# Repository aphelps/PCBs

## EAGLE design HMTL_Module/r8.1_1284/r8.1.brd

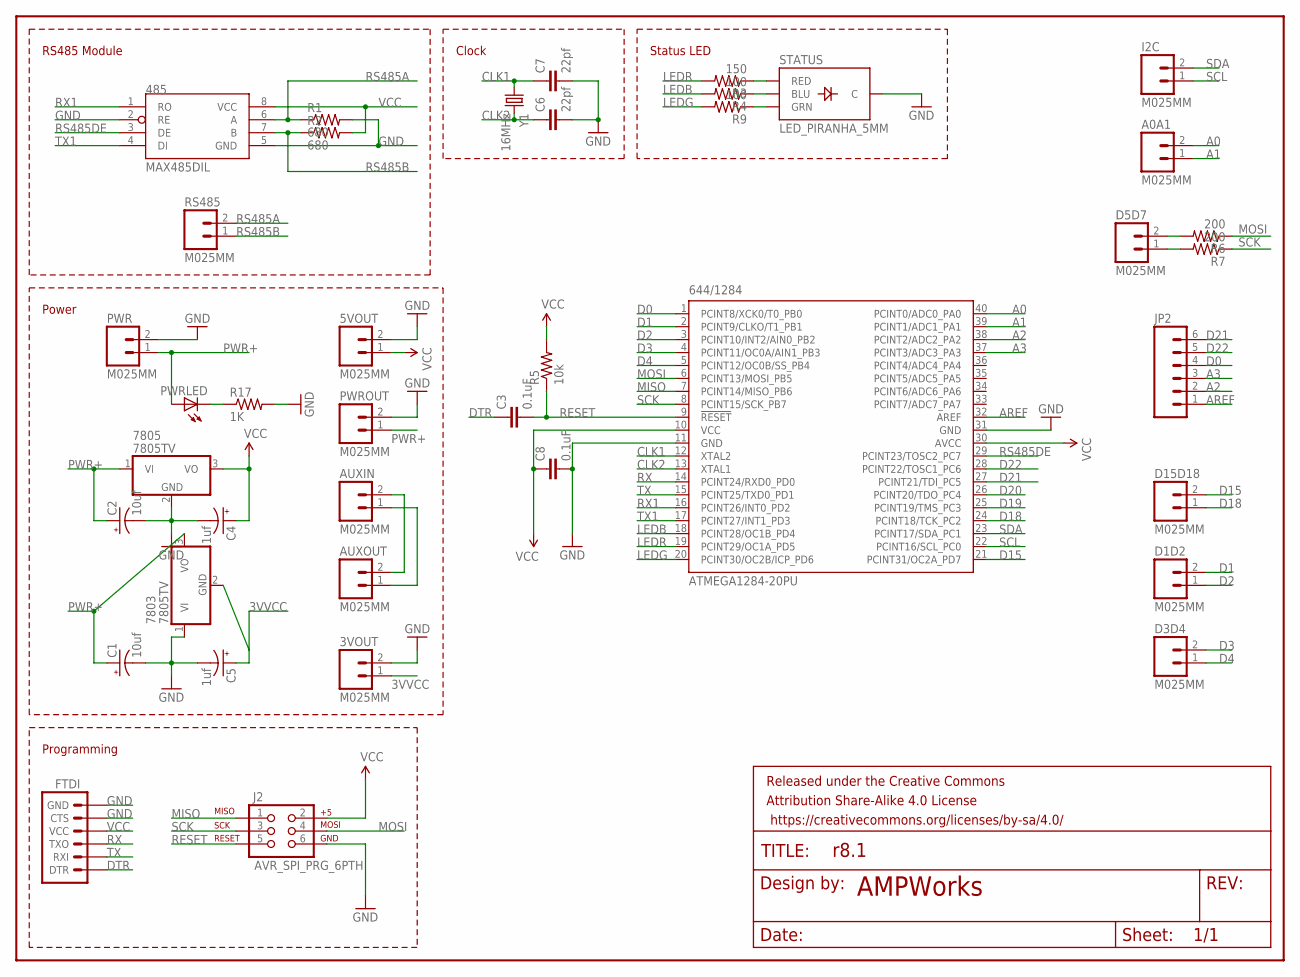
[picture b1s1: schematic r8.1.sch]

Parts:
3VOUT, 5VOUT: M025MM; SCREWTERMINAL-5MM-2
485: MAX485DIL; DIL08
644/1284: ATMEGA1284-20PU; DIL40
7803, 7805: 7805TV; TO220V
A0A1: M025MM; SCREWTERMINAL-5MM-2
AUXIN: M025MM; SCREWTERMINAL-5MM-2
AUXOUT: M025MM; SCREWTERMINAL-5MM-2
C1, C2: 10uf; CPOL-RADIAL-10UF-25V
C3, C8: 0.1uF; CAP-PTH-SMALL
C4, C5: 1uf; CPOL-RADIAL-10UF-25V
C6, C7: 22pf; CAP-PTH-SMALL
D1D2, D3D4, D5D7, D15D18: M025MM; SCREWTERMINAL-5MM-2
FRAME1: FRAME-LETTER; CREATIVE_COMMONS
FTDI: ARDUINO_SERIAL_PROGRAMPTH; 1X06
I2C: M025MM; SCREWTERMINAL-5MM-2
J2: AVR_SPI_PRG_6PTH; 2X3
JP2: M06NO_SILK; 1X06_NO_SILK
PWR: M025MM; SCREWTERMINAL-5MM-2
PWRLED: LED5MM
PWROUT: M025MM; SCREWTERMINAL-5MM-2
R1, R2: 680; AXIAL-0.4
R3: 150; AXIAL-0.4
R4, R9: 100; AXIAL-0.4
R5: 10k; AXIAL-0.4
R6, R7: 200; AXIAL-0.4
R17: 1K; AXIAL-0.4
RS485: M025MM; SCREWTERMINAL-5MM-2
STATUS: LED_PIRANHA_5MM
Y1: 16MHz; HC49US

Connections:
3VVCC: 3VOUT.1, 7803.2 (GND), C5.1 (+)
A0: 644/1284.40 (PCINT0/ADC0_PA0), A0A1.2
A1: 644/1284.39 (PCINT1/ADC1_PA1), A0A1.1
A2: 644/1284.38 (PCINT2/ADC2_PA2), JP2.2
A3: 644/1284.37 (PCINT3/ADC3_PA3), JP2.3
AREF: 644/1284.32 (AREF), JP2.1
CLK1: 644/1284.12 (XTAL2), C7.1, Y1.1
CLK2: 644/1284.13 (XTAL1), C6.1, Y1.2
D0: 644/1284.1 (PCINT8/XCK0/T0_PB0), JP2.4
D1: 644/1284.2 (PCINT9/CLKO/T1_PB1), D1D2.2
D2: 644/1284.3 (PCINT10/INT2/AIN0_PB2), D1D2.1
D3: 644/1284.4 (PCINT11/OC0A/AIN1_PB3), D3D4.2
D4: 644/1284.5 (PCINT12/OC0B/SS_PB4), D3D4.1
D15: 644/1284.21 (PCINT31/OC2A_PD7), D15D18.2
D18: 644/1284.24 (PCINT18/TCK_PC2), D15D18.1
D19: 644/1284.25 (PCINT19/TMS_PC3)
D20: 644/1284.26 (PCINT20/TDO_PC4)
D21: 644/1284.27 (PCINT21/TDI_PC5), JP2.6
D22: 644/1284.28 (PCINT22/TOSC1_PC6), JP2.5
DTR: C3.1, FTDI.DTR
GND: 3VOUT.2, 5VOUT.2, 485.2 (RE), 485.5 (GND), 644/1284.11 (GND), 644/1284.31 (GND), 7803.1 (VI), 7805.2 (GND), C1.2 (-), C2.2 (-), C4.2 (-), C5.2 (-), C6.2, C7.2, C8.2, FTDI.CTS, FTDI.GND, J2.6, PWR.2, PWROUT.2, R1.P$2 (2), R17.P$2 (2), STATUS.- (C)
LEDB: 644/1284.18 (PCINT28/OC1B_PD4), R4.P$2 (2)
LEDG: 644/1284.20 (PCINT30/OC2B/ICP_PD6), R9.P$2 (2)
LEDR: 644/1284.19 (PCINT29/OC1A_PD5), R3.P$2 (2)
MISO: 644/1284.7 (PCINT14/MISO_PB6), J2.1
MOSI: 644/1284.6 (PCINT13/MOSI_PB5), J2.4, R6.P$1 (1)
unnamed: PWRLED.K (C), R17.P$1 (1)
unnamed: AUXIN.1, AUXOUT.1
unnamed: AUXIN.2, AUXOUT.2
unnamed: D5D7.2, R6.P$2 (2)
unnamed: R3.P$1 (1), STATUS.R (RED)
unnamed: R4.P$1 (1), STATUS.B (BLU)
unnamed: R9.P$1 (1), STATUS.G (GRN)
unnamed: D5D7.1, R7.P$2 (2)
PWR+: 7803.3 (VO), 7805.1 (VI), C1.1 (+), C2.1 (+), PWR.1, PWRLED.A, PWROUT.1
RESET: 644/1284.9 (!RESET), C3.2, J2.5, R5.P$1 (1)
RS485A: 485.6 (A), R1.P$1 (1), RS485.2
RS485B: 485.7 (B), R2.P$1 (1), RS485.1
RS485DE: 485.3 (DE), 644/1284.29 (PCINT23/TOSC2_PC7)
RX: 644/1284.14 (PCINT24/RXD0_PD0), FTDI.TXO
RX1: 485.1 (RO), 644/1284.16 (PCINT26/INT0_PD2)
SCK: 644/1284.8 (PCINT15/SCK_PB7), J2.3, R7.P$1 (1)
SCL: 644/1284.22 (PCINT16/SCL_PC0), I2C.1
SDA: 644/1284.23 (PCINT17/SDA_PC1), I2C.2
TX: 644/1284.15 (PCINT25/TXD0_PD1), FTDI.RXI
TX1: 485.4 (DI), 644/1284.17 (PCINT27/INT1_PD3)
VCC: 5VOUT.1, 485.8 (VCC), 644/1284.10 (VCC), 644/1284.30 (AVCC), 7805.3 (VO), C4.1 (+), C8.1, FTDI.VCC, J2.2, R2.P$2 (2), R5.P$2 (2)

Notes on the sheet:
RS485 Module
Programming
Power
AMPWorks
Clock
Status LED

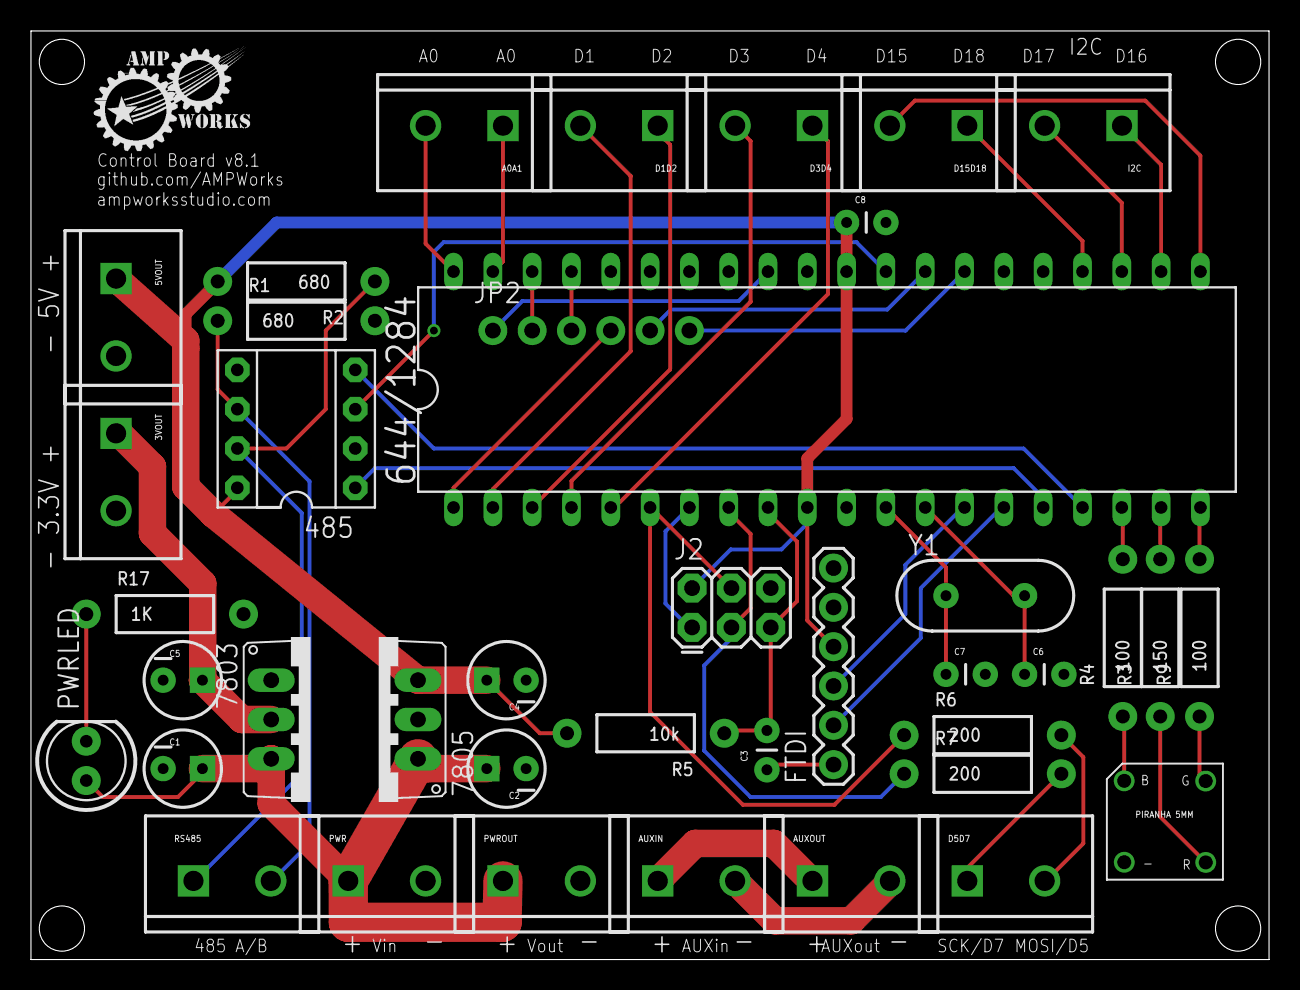
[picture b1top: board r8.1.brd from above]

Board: 2 copper layers, 80.0 x 60.0 mm, 41 parts (0 on the bottom side), 45 nets.

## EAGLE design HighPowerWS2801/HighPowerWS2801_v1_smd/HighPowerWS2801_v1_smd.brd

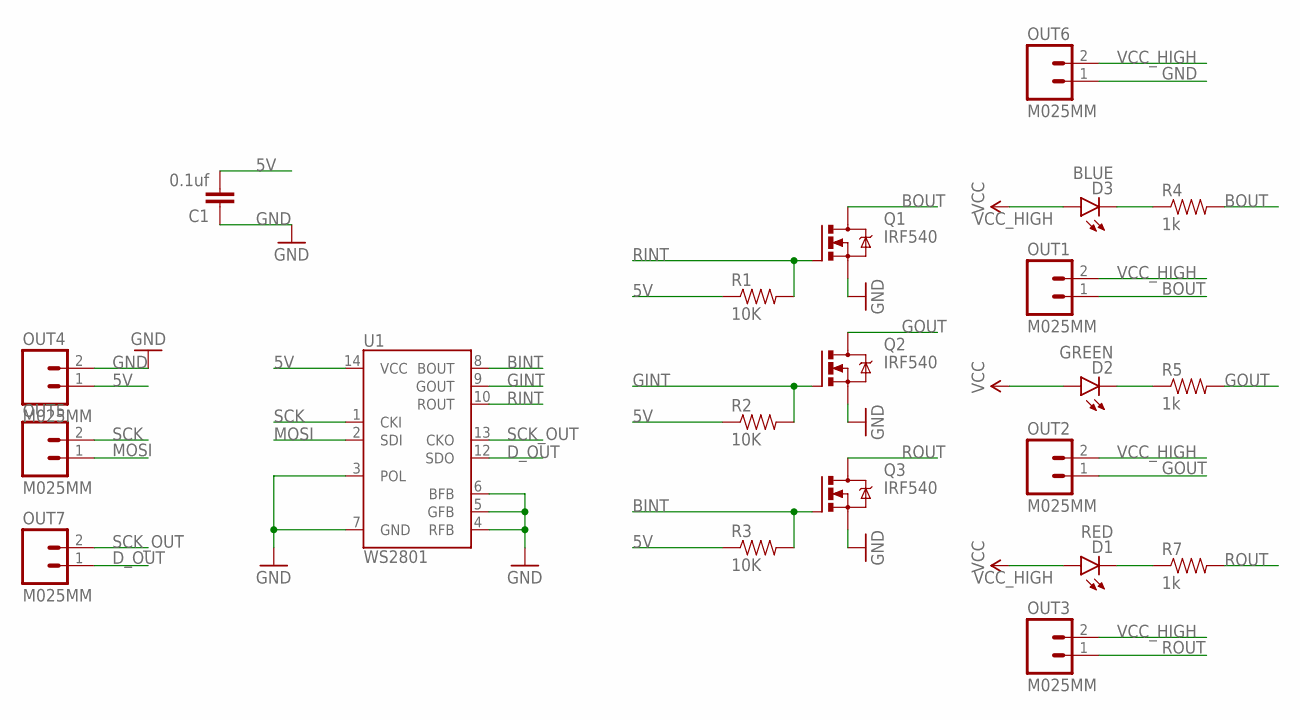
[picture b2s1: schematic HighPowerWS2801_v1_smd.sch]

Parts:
C1: 0.1uf; 0603-CAP
D1: RED; LED-0603
D2: GREEN; LED-0603
D3: BLUE; LED-0603
OUT1, OUT2, OUT3, OUT4, OUT5, OUT6, OUT7: M025MM; SCREWTERMINAL-5MM-2
Q1, Q2, Q3: IRF540; TO220BV
R1, R2, R3: 10K; 0603-RES
R4, R5, R7: 1k; 0603-RES
U1: WS2801; SOP-14

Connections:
5V: C1.2, OUT4.1, R1.1, R2.1, R3.1, U1.14 (VCC)
BINT: Q3.G, R3.2, U1.8 (BOUT)
BOUT: OUT1.1, Q1.D, R4.2
D_OUT: OUT7.1, U1.12 (SDO)
GINT: Q2.G, R2.2, U1.9 (GOUT)
GND: C1.1, OUT4.2, OUT6.1, Q1.S, Q2.S, Q3.S, U1.3 (POL), U1.4 (RFB), U1.5 (GFB), U1.6 (BFB), U1.7 (GND)
GOUT: OUT2.1, Q2.D, R5.2
MOSI: OUT5.1, U1.2 (SDI)
unnamed: D3.C, R4.1
unnamed: D2.C, R5.1
unnamed: D1.C, R7.1
RINT: Q1.G, R1.2, U1.10 (ROUT)
ROUT: OUT3.1, Q3.D, R7.2
SCK: OUT5.2, U1.1 (CKI)
SCK_OUT: OUT7.2, U1.13 (CKO)
VCC_HIGH: D1.A, D2.A, D3.A, OUT1.2, OUT2.2, OUT3.2, OUT6.2

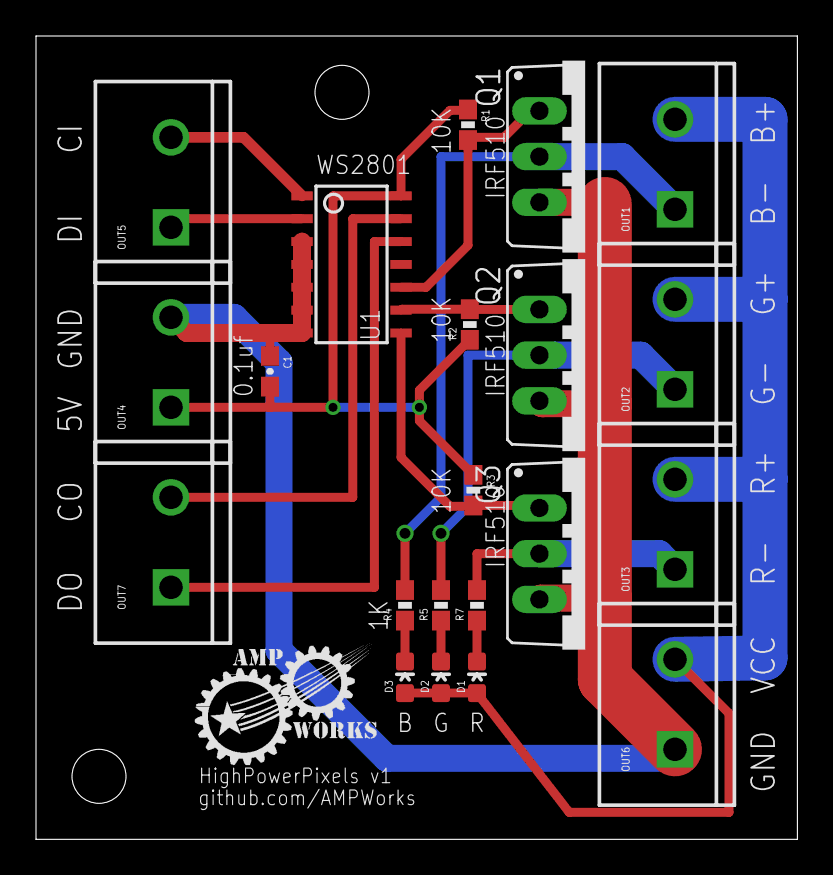
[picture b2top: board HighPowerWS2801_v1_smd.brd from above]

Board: 2 copper layers, 42.3 x 44.6 mm, 21 parts (0 on the bottom side), 16 nets.

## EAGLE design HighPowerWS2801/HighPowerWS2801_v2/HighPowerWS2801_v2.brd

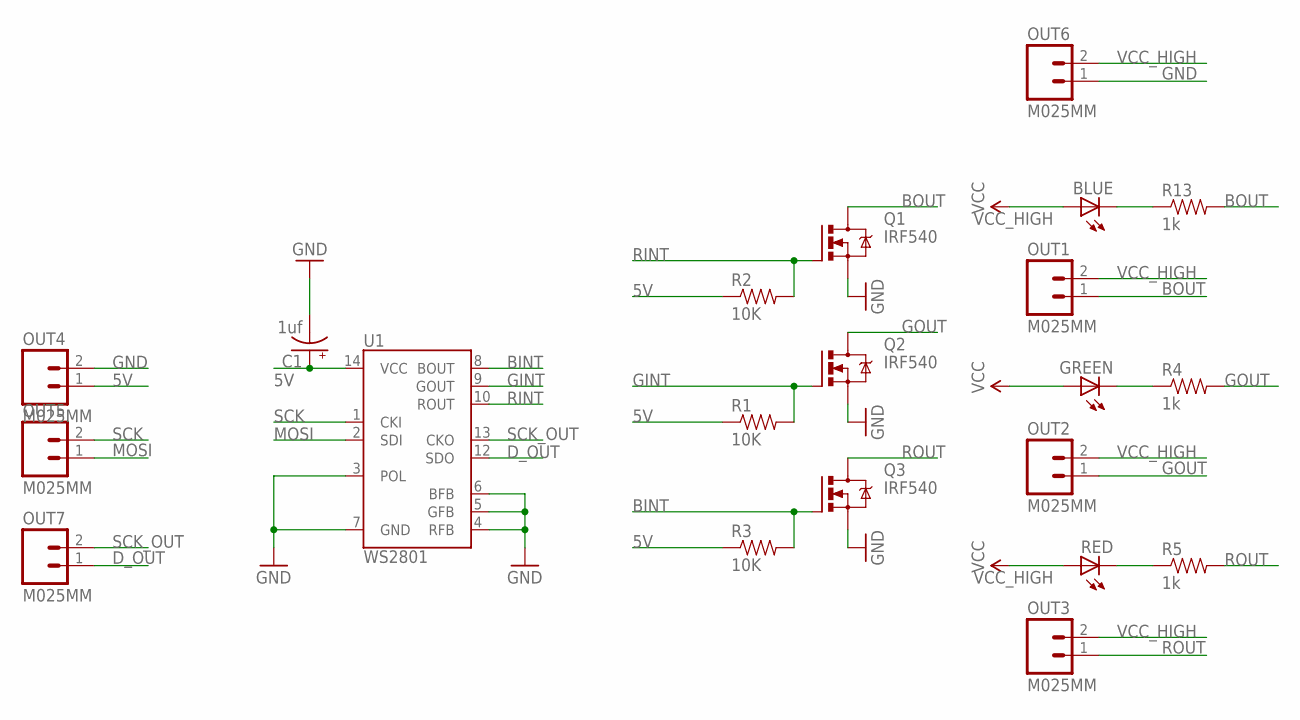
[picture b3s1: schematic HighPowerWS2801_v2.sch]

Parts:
BLUE: LED3MM
C1: 1uf; CPOL-RADIAL-10UF-25V
GREEN: LED3MM
OUT1, OUT2, OUT3, OUT4, OUT5, OUT6, OUT7: M025MM; SCREWTERMINAL-5MM-2
Q1, Q2, Q3: IRF540; TO220BV
R1, R2, R3: 10K; AXIAL-0.4
R4, R5, R13: 1k; AXIAL-0.4
RED: LED3MM
U1: WS2801; SOP-14

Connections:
5V: C1.1 (+), OUT4.1, R1.P$1 (1), R2.P$1 (1), R3.P$1 (1), U1.14 (VCC)
BINT: Q3.G, R3.P$2 (2), U1.8 (BOUT)
BOUT: OUT1.1, Q1.D, R13.P$2 (2)
D_OUT: OUT7.1, U1.12 (SDO)
GINT: Q2.G, R1.P$2 (2), U1.9 (GOUT)
GND: C1.2 (-), OUT4.2, OUT6.1, Q1.S, Q2.S, Q3.S, U1.3 (POL), U1.4 (RFB), U1.5 (GFB), U1.6 (BFB), U1.7 (GND)
GOUT: OUT2.1, Q2.D, R4.P$2 (2)
MOSI: OUT5.1, U1.2 (SDI)
unnamed: BLUE.K (C), R13.P$1 (1)
unnamed: GREEN.K (C), R4.P$1 (1)
unnamed: R5.P$1 (1), RED.K (C)
RINT: Q1.G, R2.P$2 (2), U1.10 (ROUT)
ROUT: OUT3.1, Q3.D, R5.P$2 (2)
SCK: OUT5.2, U1.1 (CKI)
SCK_OUT: OUT7.2, U1.13 (CKO)
VCC_HIGH: BLUE.A, GREEN.A, OUT1.2, OUT2.2, OUT3.2, OUT6.2, RED.A

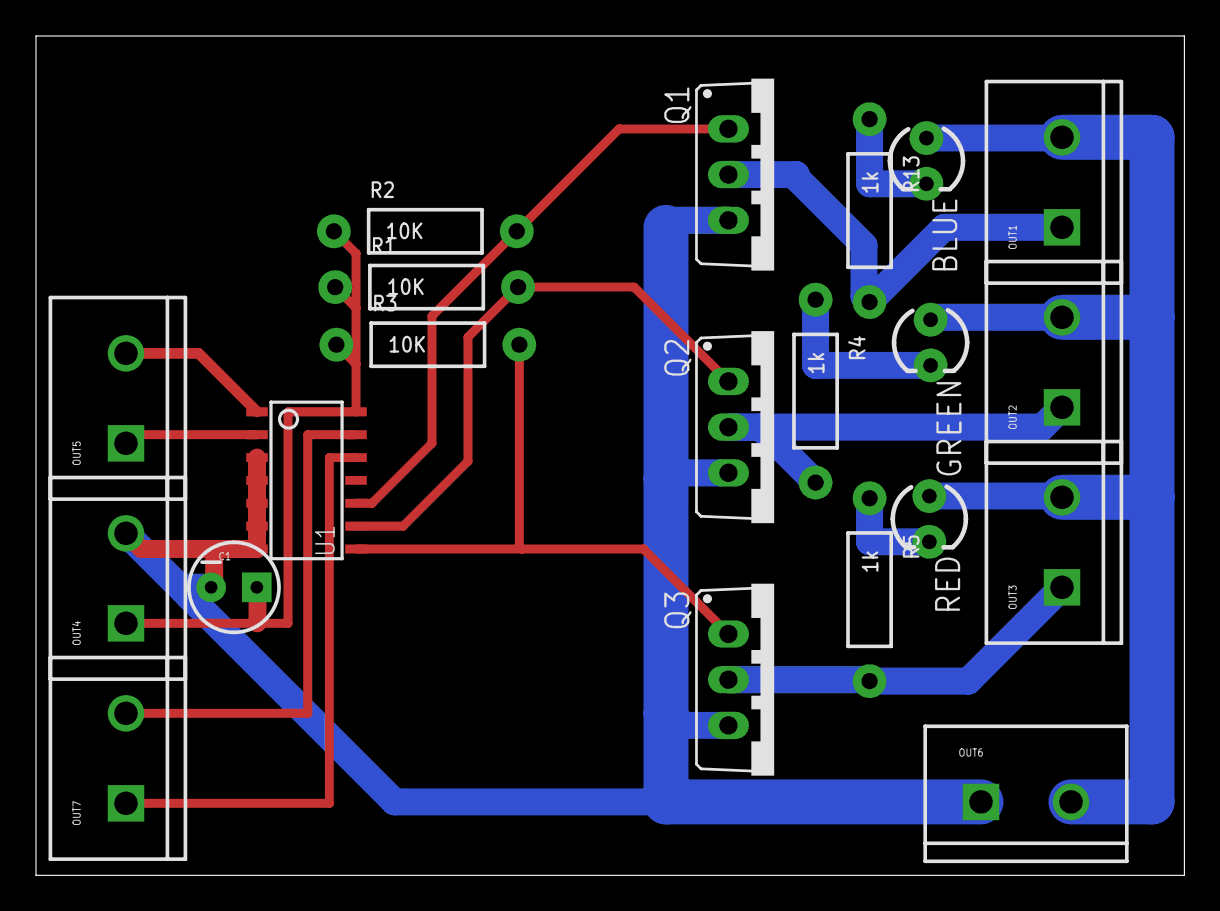
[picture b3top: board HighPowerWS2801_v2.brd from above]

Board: 2 copper layers, 63.8 x 46.6 mm, 21 parts (0 on the bottom side), 16 nets.

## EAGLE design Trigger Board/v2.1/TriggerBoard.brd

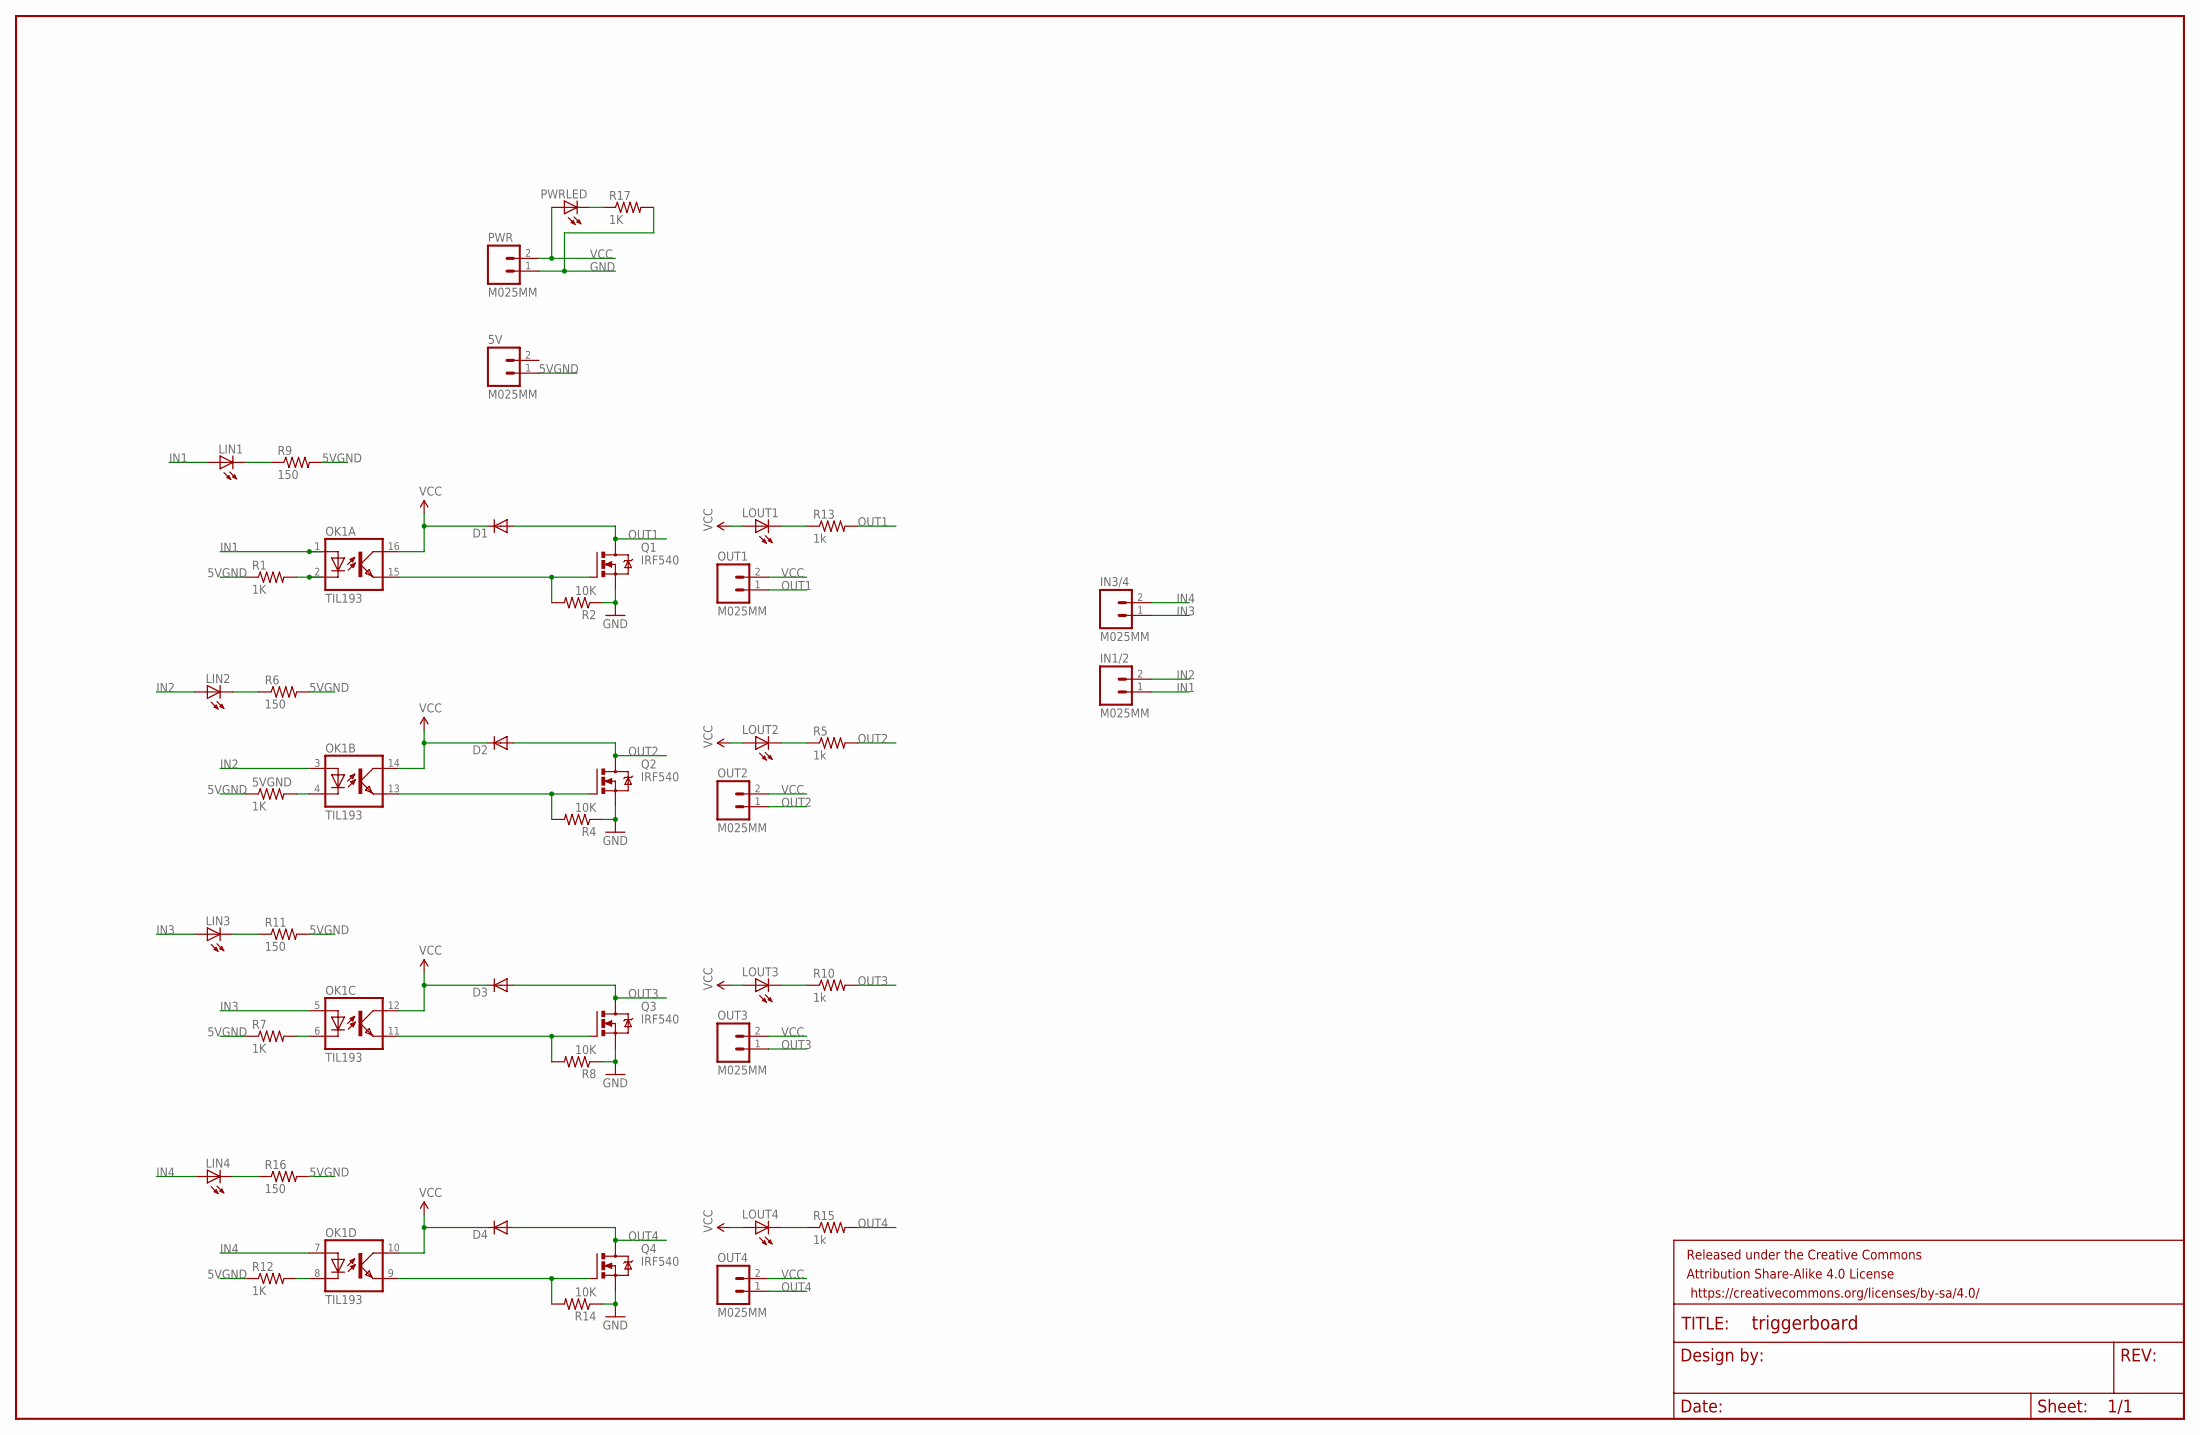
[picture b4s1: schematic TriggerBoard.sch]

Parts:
5V: M025MM; SCREWTERMINAL-5MM-2
5VGND: 1K; AXIAL-0.4
D1, D2, D3, D4: DIODEPTH; DIODE-1N4001
FRAME1: FRAME-LEDGER; CREATIVE_COMMONS
IN1/2, IN3/4: M025MM; SCREWTERMINAL-5MM-2
LIN1, LIN2, LIN3, LIN4: LED3MM
LOUT1, LOUT2, LOUT3, LOUT4: LED3MM
OK1: TIL193; DIL16
OUT1, OUT2, OUT3, OUT4: M025MM; SCREWTERMINAL-5MM-2
PWR: M025MM; SCREWTERMINAL-5MM-2
PWRLED: LED5MM
Q1, Q2, Q3, Q4: IRF540; TO220BV
R1, R7, R12, R17: 1K; AXIAL-0.4
R2, R4, R8, R14: 10K; AXIAL-0.4
R5, R10, R13, R15: 1k; AXIAL-0.4
R6, R9, R11, R16: 150; AXIAL-0.4

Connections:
5VGND: 5V.1, 5VGND.P$1 (1), R1.P$1 (1), R6.P$2 (2), R7.P$1 (1), R9.P$2 (2), R11.P$2 (2), R12.P$1 (1), R16.P$2 (2)
GND: PWR.1, Q1.S, Q2.S, Q3.S, Q4.S, R2.P$1 (1), R4.P$1 (1), R8.P$1 (1), R14.P$1 (1), R17.P$2 (2)
IN1: IN1/2.1, LIN1.A, OK1.1 (A)
IN2: IN1/2.2, LIN2.A, OK1.3 (A)
IN3: IN3/4.1, LIN3.A, OK1.5 (A)
IN4: IN3/4.2, LIN4.A, OK1.7 (A)
unnamed: LOUT1.K (C), R13.P$1 (1)
unnamed: 5VGND.P$2 (2), OK1.4 (C)
unnamed: LIN1.K (C), R9.P$1 (1)
unnamed: OK1.15 (EMIT), Q1.G, R2.P$2 (2)
unnamed: OK1.13 (EMIT), Q2.G, R4.P$2 (2)
unnamed: OK1.2 (C), R1.P$2 (2)
unnamed: LOUT2.K (C), R5.P$1 (1)
unnamed: LIN2.K (C), R6.P$1 (1)
unnamed: OK1.11 (EMIT), Q3.G, R8.P$2 (2)
unnamed: LOUT3.K (C), R10.P$1 (1)
unnamed: OK1.6 (C), R7.P$2 (2)
unnamed: LIN3.K (C), R11.P$1 (1)
unnamed: OK1.9 (EMIT), Q4.G, R14.P$2 (2)
unnamed: LOUT4.K (C), R15.P$1 (1)
unnamed: OK1.8 (C), R12.P$2 (2)
unnamed: LIN4.K (C), R16.P$1 (1)
unnamed: PWRLED.K (C), R17.P$1 (1)
OUT1: D1.A, OUT1.1, Q1.D, R13.P$2 (2)
OUT2: D2.A, OUT2.1, Q2.D, R5.P$2 (2)
OUT3: D3.A, OUT3.1, Q3.D, R10.P$2 (2)
OUT4: D4.A, OUT4.1, Q4.D, R15.P$2 (2)
VCC: D1.C, D2.C, D3.C, D4.C, LOUT1.A, LOUT2.A, LOUT3.A, LOUT4.A, OK1.10 (COL), OK1.12 (COL), OK1.14 (COL), OK1.16 (COL), OUT1.2, OUT2.2, OUT3.2, OUT4.2, PWR.2, PWRLED.A

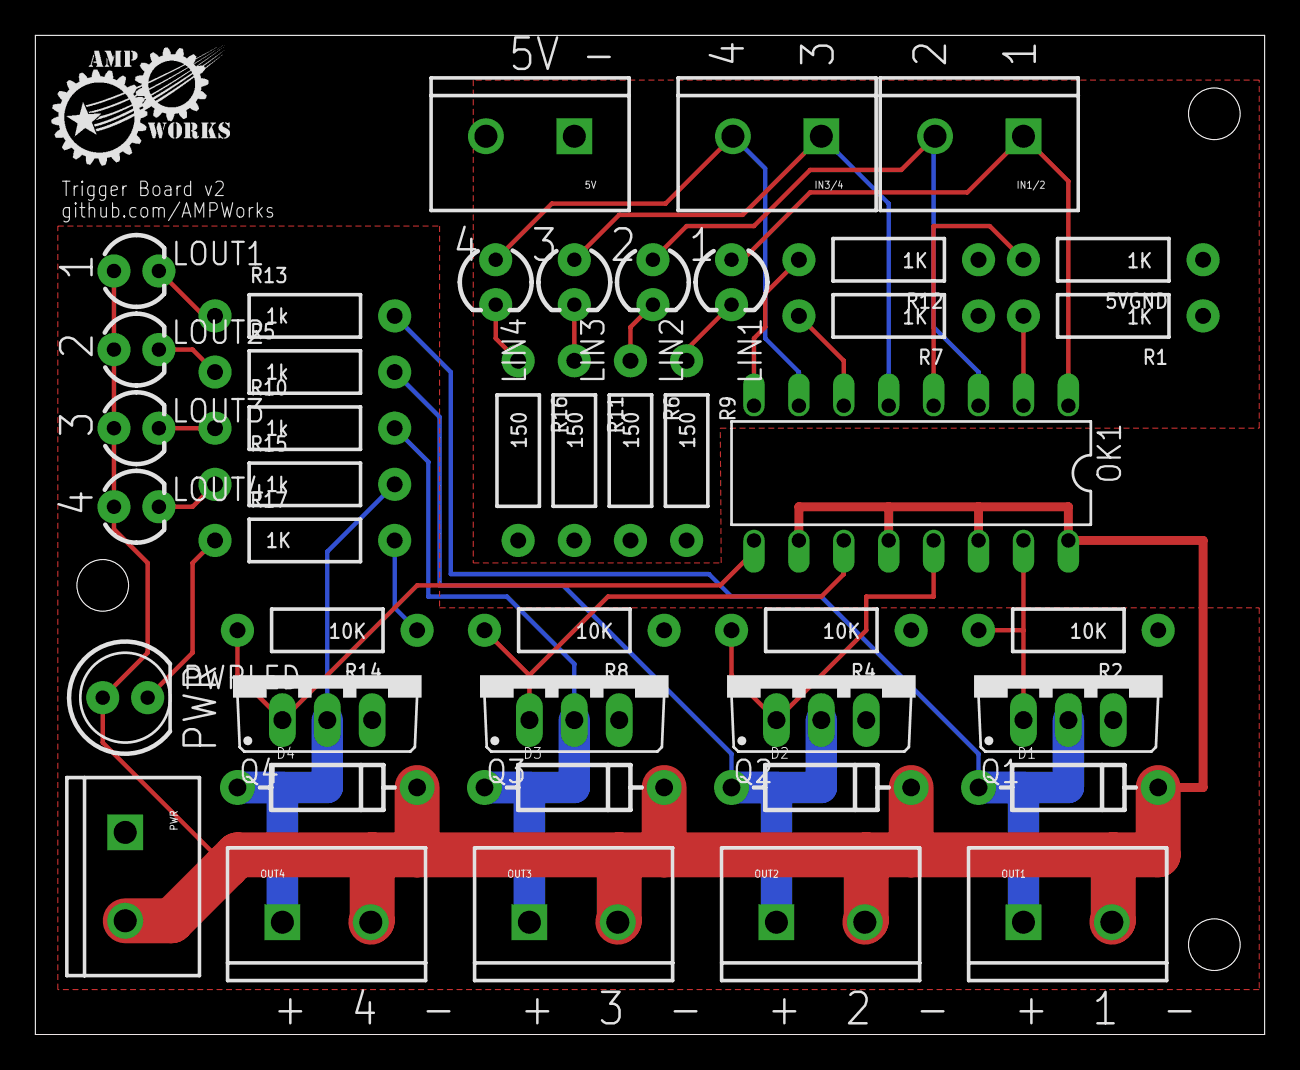
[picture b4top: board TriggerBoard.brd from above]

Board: 2 copper layers, 69.5 x 56.5 mm, 44 parts (0 on the bottom side), 28 nets.

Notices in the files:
parts and their libraries:
SparkFun-Connectors: Licensing: Creative Commons ShareAlike 4.0 International - https://creativecommons.org/licenses/by-sa/4.0
SparkFun-Aesthetics: Released under the Creative Commons Attribution Share-Alike 4.0 License
SparkFun-Aesthetics: https://creativecommons.org/licenses/by-sa/4.0
